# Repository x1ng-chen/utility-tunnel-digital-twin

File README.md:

# 综合管廊数字孪生与三Agent运维系统

面向综合管廊教学台架与智能运维演示，连接 **30路启用传感器、四块STM32、ESP32-S3网关、三维孪生、三Agent工作流和“小管”语音终端**。

[参赛版项目总览](docs/competition-final/01-项目总览.md) · [Agent 技术详解](docs/competition-final/05-Agent技术亮点与实现.md) · [当前进度](docs/PROJECT_STATUS.md) · [文档导航](docs/README.md) · [完整业务固件](firmware/four-controller/RELEASE.md) · [协作规范](CONTRIBUTING.md) · [版本记录](CHANGELOG.md)

> 参赛版 · 2026-11-07。11 月 6 日完成两轮 P5 实物告警、三维定位、真实三 Agent 排障与人工结单。第二轮核对 38 条平台观测与网关 MQTT 报文。模型复核仍要求补证，人工另行记录现场核对结果后完成工单。[实测记录](docs/competition-final/03-P5实物验收与证据.md)

*工作台截图来自2026-10-29隔离模拟环境，不是实时硬件状态。*

## 当前能力

| 模块 | 已具备的能力 | 验证与限制 |
| --- | --- | --- |
| 三Agent运维 | 取证→诊断→复核；工具轨迹、引用、快照与版本可追溯 | P5 两轮真实 DeepSeek 三角色均有输出，最终复核要求修改；独立人工评分待完成 |
| 可续查排障 | 候选原因、反证、缺项、人工检查反馈、新快照续查 | 人工报告不冒充仪表测量，不自动结单 |
| 受控经验与流程 | 候选提取、管理员审核、版本与来源匹配、退役 | 未审批内容不注入；复核通过不等于根因已证实 |
| 本地只读决策 | AnyJev/Tacit闭集检查选择、超时或不合格回退 | 默认关闭，不替代诊断模型，不具有任意控制权限 |
| 三维孪生 | V24统一编号、31路独立定位、明显告警高亮、风机状态呈现 | 五路火焰触发/定位/恢复获用户确认；其他逐路验收未齐 |
| 现场采集 | 四STM32分区采集，RS-485→单S3网关→MQTT→Django | 已有四板上报记录；CTRL-02 温湿度已停用，四板仍持续上报 |
| 双风机 | 固件支持继电器、反相PWM、TACH与INA226反馈 | 用户确认两台曾转动；调速、测速、支路电流精度仍待验收 |
| 小管语音 | 独立 S3 语音终端、唤醒、OLED、音量与站点只读巡检 | 现场已听到 P5 播报；语音端不负责设备控制与工单操作 |
| 仿真与成本 | 人工确认的仿真处置、回执复盘、双风机能耗/任务成本 | 模拟、假设与实测分别展示，不宣称真实节能收益 |

## 架构

```mermaid
flowchart LR
  S[五检测站 / 30路启用] --> C[4 × STM32F103RCT6]
  C <-->|RS-485 / Modbus RTU| G[ESP32-S3汇总网关]
  G -->|Wi-Fi / MQTT| M[MQTT接入服务]
  M --> D[Django / 数据与权限]
  D <--> W[Vue / Three.js / Agent工作台]
  D <--> A[取证Agent → 诊断Agent → 复核Agent]
  A --> E[证据护栏 / 知识检索 / 审核经验]
  V[另一块ESP32-S3语音终端] <--> VS[小管语音服务]
  VS <--> D
```

设备命令、命令回执、输出状态、独立转速反馈和告警恢复是不同证据。**实物只读联调不开放网页硬件控制；仿真执行不计作真实MQTT/RS-485验收。**

## 实体与身份基线

实体外形 **700 × 700 × 300 mm**，四角主控、五检测站，两台排风机，无水泵。传感器为液位4、温湿度4、MQ-2/MQ-4/MQ-7各5、火焰5、氧气3，共31个登记点位。2号板温湿度已停用，当前启用30路。两路INA226独立统计。

| 主控 | 电气布局位置 | 物理传感器数 | 主要设备 |
| --- | --- | ---: | --- |
| CTRL-01 | 左下 | 11 | 状态副屏 |
| CTRL-02 | 右下 | 7 | 主屏、摇杆、FAN-02、继电器2、INA226-FAN2 |
| CTRL-03 | 右上 | 6 | 蜂鸣器、灯带 |
| CTRL-04 | 左上 | 7 | FAN-01、继电器1、INA226-FAN1 |

采集编号、平台资产编码、模型文字及网格绑定通过版本化清单对应；不根据数组顺序重编号。P5没有温湿度模块。实物前端使用V24统一编号；隔离软件演示仍支持按精确SHA安装V24，不能混用映射。

[接线与引脚](docs/hardware/four-controller-wiring-20261026/README.md) · [风机/继电器/INA接线](docs/hardware/fan-relay-ina226-wiring-20261029.md) · [模型版本](model/README.md)

## 获取与启动

```powershell
git clone https://github.com/x1ng-chen/utility-tunnel-digital-twin.git
cd utility-tunnel-digital-twin
git lfs install
git lfs pull
```

需要Python 3.12、Node.js 22或更高兼容版本、Git LFS。嵌入式构建另需ARM GCC、CMake、Ninja与PlatformIO；依赖以各模块锁文件为准。

| 使用方式 | 入口 | 数据与权限 |
| --- | --- | --- |
| 隔离软件演示 | [Windows/Docker启动](deploy/agent-demo/README.md)；默认 `http://127.0.0.1:5187/agent-workbench` | 模拟库；模型调用默认关闭，需显式启用 |
| 参赛评审版 | [独立部署](deploy/competition-review/README.md) · [评审操作](docs/competition-final/04-比赛提交与评审演示.md) | P5 历史实测回放，查看者可运行只读 Agent 任务。公网地址需实测验收 |
| 实物只读联调 | [启动说明](deploy/hardware-live/README.md)；默认前端5173/API8000 | `.hardware-live/`独立库；不发布硬件命令 |
| 小管语音 | [语音服务](services/README.md) 与 [语音终端](firmware/README.md) | 使用独立S3，沿用其专门配置与启动说明 |
| 完整固件 | [构建/发布/刷写](firmware/four-controller/RELEASE.md) | 四STM32＋网关业务镜像；2号不使用最小诊断版作发布镜像 |

**账号、密码、Wi-Fi及MQTT凭据不放在主页或固件中。** 启动器生成的访问文件与`.env`仅保存在被忽略的本地运行目录。示例配置不包含真实密钥。

## 验证与待办

上一轮固件指纹和软件测试见[发布验证](docs/releases/2026-10-31/README.md)。本轮实物及模型记录见[P5 验收](docs/competition-final/03-P5实物验收与证据.md)。普通测试不调用付费模型、不连接真实执行器；浏览器、容器、真实模型与实物结论单独记录。

接下来优先完成：

1. 验收独立评审版公网登录、三维加载和巡检、排障、复核三项只读任务。
2. 双风机PWM/TACH和INA支路反馈专项验收，逐路完成其余传感器触发/恢复。
3. 显式启动真实DeepSeek回归、单/三Agent同数据对照及独立人工评分。
4. 整机断线恢复及连续运行复测。

K210视觉、趋势预测、MCP和寿命预测未纳入当前交付；仓库历史规划不代表这些功能已实现。

## 仓库结构

```text
backend/       Django API、三Agent、权限、场景与评测
frontend/      Vue工作台、Three.js孪生及界面测试
firmware/      四主控/网关业务源码、语音终端及历史固件
services/      MQTT接入、本地决策、语音服务
model/         V24统一编号及保留的历史模型交付
hardware/      硬件设计与说明
deploy/        隔离演示、只读联调和部署工具
docs/          当前进度、模块说明、验证记录与历史资料
tools/         质量门禁、模型检查与复现工具
```

旧README已归档到[历史说明](docs/history/README-before-20261031.md)。涉及双节点、旧模型、旧引脚和旧验收的记录保留出处，不作为当前操作依据。

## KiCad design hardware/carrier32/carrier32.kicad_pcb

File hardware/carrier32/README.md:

# Carrier32 KiCad 工程

本目录实现 `docs/superpowers/specs/2026-09-22-dual-node-32-sensor-carrier-design.md`。

## 工具链

- KiCad 10.0.5：`D:\KiCad\bin\kicad-cli.exe`
- Python 3：设计输入、网络合同及制造包检查脚本
- PowerShell：统一检查入口 `scripts/run_checks.ps1`

已安装的辅助能力包括 `kicad-tool`、`kicad-workflow`、
`kicad-sch-cleanup-loop`、`manage-pcba-program`、
`qualify-pcba-sourcing`、`design-and-review-circuit`、
`schematic-humanizer`、`pcb-layout-review`、
`release-pcba-fabrication`，以及 kicad-happy 的 `kicad`、`emc`、`bom`。
这些能力从下一轮 Codex 技能加载起可用。

## 运行检查

仅检查本机工具和工程骨架：

```powershell
powershell -ExecutionPolicy Bypass -File hardware/carrier32/scripts/run_checks.ps1 -Preflight
```

目前已经建立受保护的 12 V 输入、两路独立 5 V 降压和两路 ESP 3.3 V
电源原理图草稿，见 [电源审查记录](docs/power-review.md)。`scripts/check_power_nets.ps1`
对电源网表执行 80 项引脚映射断言；当前 ERC 为 0 错误、10 个尚未接到后续接口的警告。
导出的图面仍拥挤且标题栏未清理，因此尚未通过视觉审查。

32 个传感器数量和 MCU 引脚分配已锁定在 `config/net-contract.csv`，
不包含 DHT11。载板端 32 个统一四针传感器接口及线束边界见
[参考接口标准](docs/reference-interface-standard.md)和 `config/connector-contract.csv`；
运行 `python hardware/carrier32/scripts/check_connector_contract.py hardware/carrier32/config/connector-contract.csv hardware/carrier32/config/net-contract.csv`
可检查针位分配。完整工程检查在原理图、PCB和制造包补齐后启用。

## 当前发布状态

工程处于设计阶段。`config/design-inputs.csv` 中有 39 项制造关键实测输入尚未验证，
其中包括控制板排针、各类传感器模块引脚顺序、输出电压和机箱尺寸。
这些信息无法由软件或通用器件资料安全推断。机械尺寸、模块引脚、电气额定值及样板负载测试未完成前，
不得把本目录的任何输出作为可投产制造包。

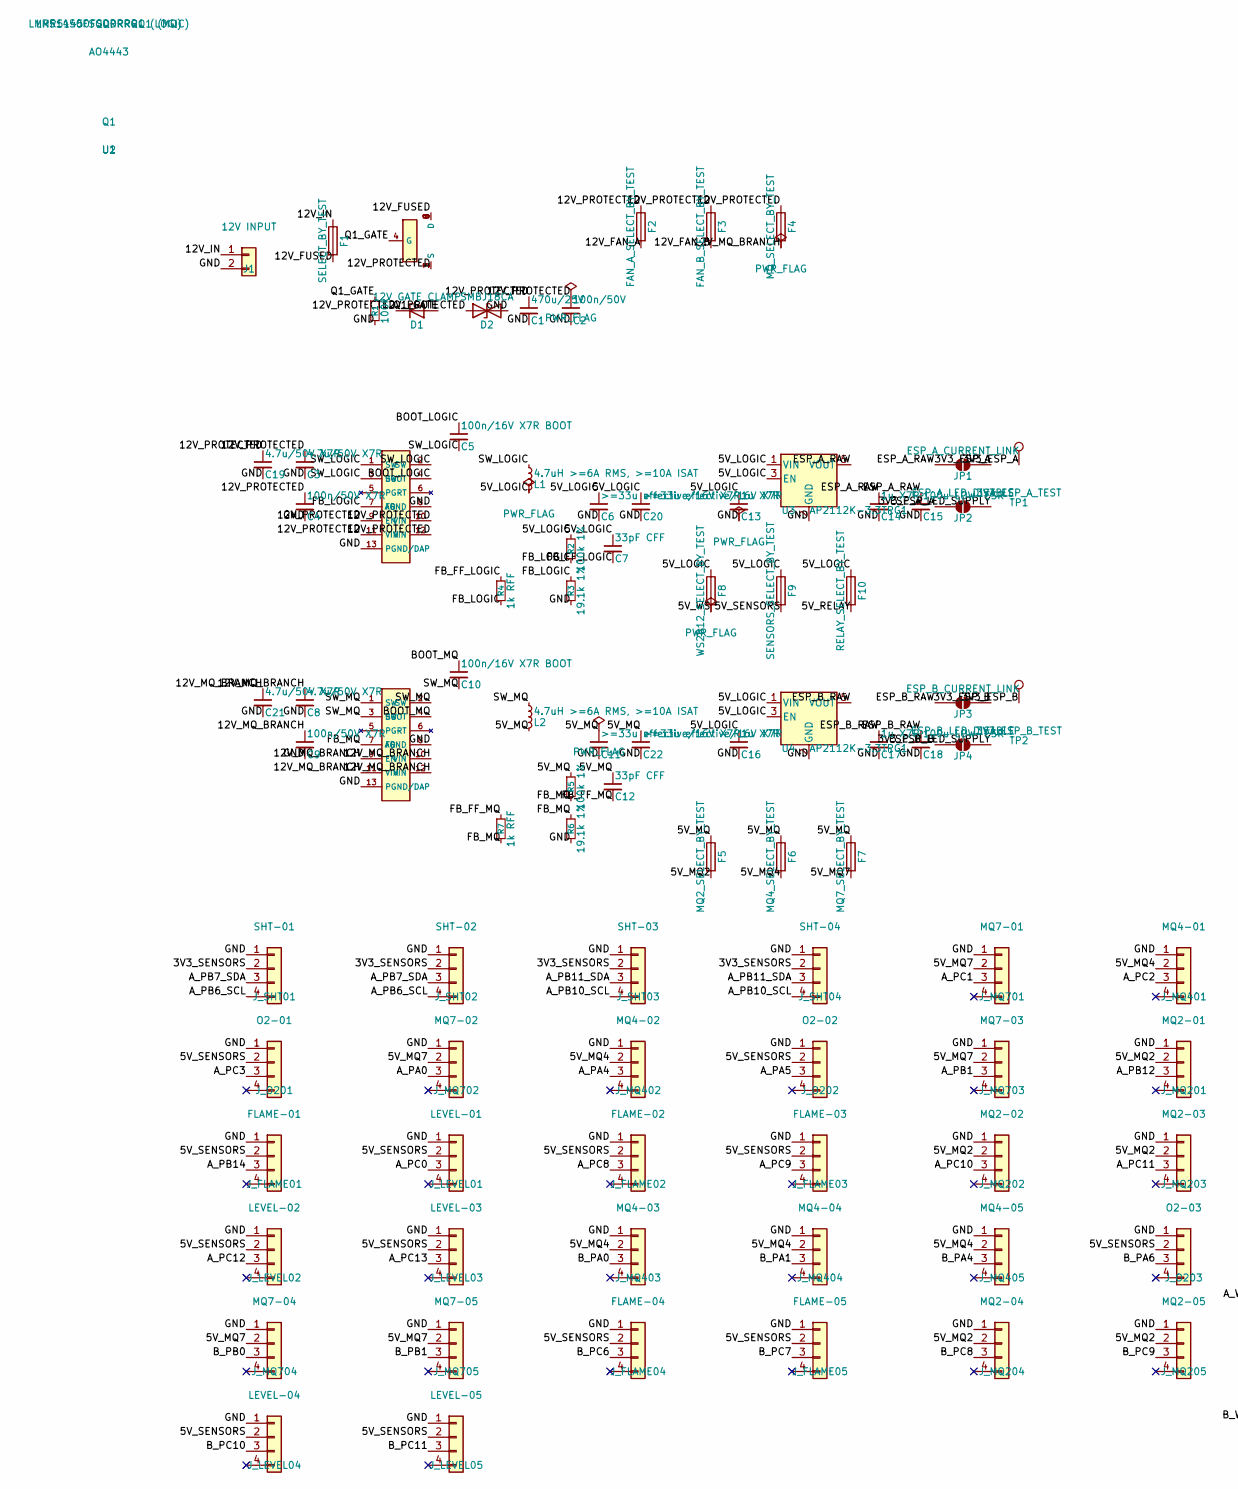
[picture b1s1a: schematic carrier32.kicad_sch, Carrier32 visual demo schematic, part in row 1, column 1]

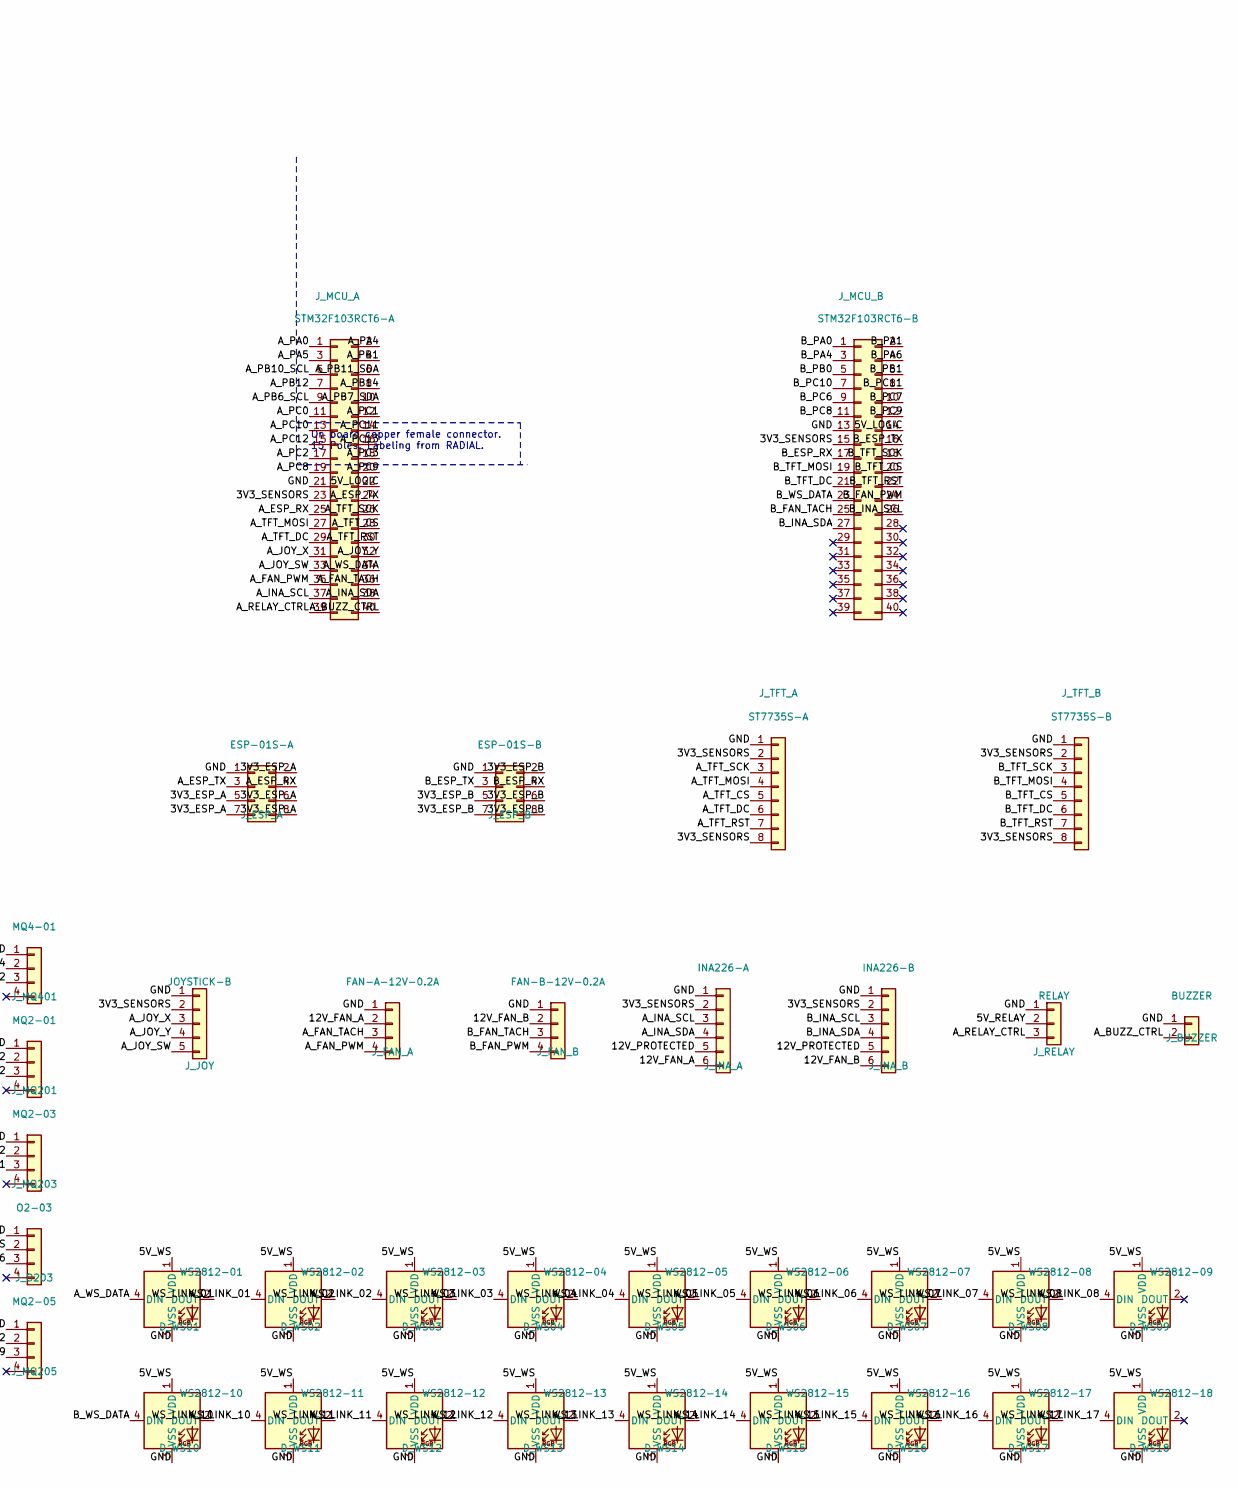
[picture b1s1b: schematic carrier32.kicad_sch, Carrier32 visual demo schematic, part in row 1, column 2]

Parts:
C1: 470u/25V; CP_Elec_10x10
C2: 100n/50V; C_0603_1608Metric
C3, C8, C19, C21: 4.7u/50V X7R; C_1210_3225Metric
C4, C9: 100n/50V X7R; C_0603_1608Metric
C5, C10: 100n/16V X7R BOOT; C_0603_1608Metric
C6, C11, C20, C22: >=33u effective/16V X7R; C_1210_3225Metric
C7, C12: 33pF CFF; C_0603_1608Metric
C13, C14, C16, C17: 1u X7R; C_0603_1608Metric
C15, C18: 100u LOW-ESR; CP_Elec_6.3x5.8
D1: 12V GATE CLAMP; D_SOD-123
D2: SMBJ18CA; D_SMB
D_WS01: WS2812-01; LED_WS2812B_PLCC4_5.0x5.0mm_P3.2mm
D_WS02: WS2812-02; LED_WS2812B_PLCC4_5.0x5.0mm_P3.2mm
D_WS03: WS2812-03; LED_WS2812B_PLCC4_5.0x5.0mm_P3.2mm
D_WS04: WS2812-04; LED_WS2812B_PLCC4_5.0x5.0mm_P3.2mm
D_WS05: WS2812-05; LED_WS2812B_PLCC4_5.0x5.0mm_P3.2mm
D_WS06: WS2812-06; LED_WS2812B_PLCC4_5.0x5.0mm_P3.2mm
D_WS07: WS2812-07; LED_WS2812B_PLCC4_5.0x5.0mm_P3.2mm
D_WS08: WS2812-08; LED_WS2812B_PLCC4_5.0x5.0mm_P3.2mm
D_WS09: WS2812-09; LED_WS2812B_PLCC4_5.0x5.0mm_P3.2mm
D_WS10: WS2812-10; LED_WS2812B_PLCC4_5.0x5.0mm_P3.2mm
D_WS11: WS2812-11; LED_WS2812B_PLCC4_5.0x5.0mm_P3.2mm
D_WS12: WS2812-12; LED_WS2812B_PLCC4_5.0x5.0mm_P3.2mm
D_WS13: WS2812-13; LED_WS2812B_PLCC4_5.0x5.0mm_P3.2mm
D_WS14: WS2812-14; LED_WS2812B_PLCC4_5.0x5.0mm_P3.2mm
D_WS15: WS2812-15; LED_WS2812B_PLCC4_5.0x5.0mm_P3.2mm
D_WS16: WS2812-16; LED_WS2812B_PLCC4_5.0x5.0mm_P3.2mm
D_WS17: WS2812-17; LED_WS2812B_PLCC4_5.0x5.0mm_P3.2mm
D_WS18: WS2812-18; LED_WS2812B_PLCC4_5.0x5.0mm_P3.2mm
F1: SELECT_BY_TEST; Fuse_1210_3225Metric
F2: FAN_A_SELECT_BY_TEST; Fuse_1210_3225Metric
F3: FAN_B_SELECT_BY_TEST; Fuse_1210_3225Metric
F4: MQ_SELECT_BY_TEST; Fuse_1210_3225Metric
F5: MQ2_SELECT_BY_TEST; Fuse_1210_3225Metric
F6: MQ4_SELECT_BY_TEST; Fuse_1210_3225Metric
F7: MQ7_SELECT_BY_TEST; Fuse_1210_3225Metric
F8: WS2812_SELECT_BY_TEST; Fuse_1210_3225Metric
F9: SENSORS_SELECT_BY_TEST; Fuse_1210_3225Metric
F10: RELAY_SELECT_BY_TEST; Fuse_1210_3225Metric
J1: 12V INPUT; TerminalBlock_Phoenix_MKDS-1,5-2_1x02_P5.00mm_Horizontal
JP1: ESP_A_CURRENT_LINK; SolderJumper-2_P1.3mm_Open_RoundedPad1.0x1.5mm
JP2: ESP_A_LED_DISABLE; SolderJumper-2_P1.3mm_Open_RoundedPad1.0x1.5mm
JP3: ESP_B_CURRENT_LINK; SolderJumper-2_P1.3mm_Open_RoundedPad1.0x1.5mm
JP4: ESP_B_LED_DISABLE; SolderJumper-2_P1.3mm_Open_RoundedPad1.0x1.5mm
J_BUZZER: BUZZER; PinSocket_1x02_P2.54mm_Vertical
J_ESP_A: ESP-01S-A; PinSocket_2x04_P2.54mm_Vertical
J_ESP_B: ESP-01S-B; PinSocket_2x04_P2.54mm_Vertical
J_FAN_A: FAN-A-12V-0.2A; JST_XH_B4B-XH-A_1x04_P2.50mm_Vertical
J_FAN_B: FAN-B-12V-0.2A; JST_XH_B4B-XH-A_1x04_P2.50mm_Vertical
J_FLAME01: FLAME-01; JST_XH_B4B-XH-A_1x04_P2.50mm_Vertical
J_FLAME02: FLAME-02; JST_XH_B4B-XH-A_1x04_P2.50mm_Vertical
J_FLAME03: FLAME-03; JST_XH_B4B-XH-A_1x04_P2.50mm_Vertical
J_FLAME04: FLAME-04; JST_XH_B4B-XH-A_1x04_P2.50mm_Vertical
J_FLAME05: FLAME-05; JST_XH_B4B-XH-A_1x04_P2.50mm_Vertical
J_INA_A: INA226-A; PinSocket_1x06_P2.54mm_Vertical
J_INA_B: INA226-B; PinSocket_1x06_P2.54mm_Vertical
J_JOY: JOYSTICK-B; PinSocket_1x05_P2.54mm_Vertical
J_LEVEL01: LEVEL-01; JST_XH_B4B-XH-A_1x04_P2.50mm_Vertical
J_LEVEL02: LEVEL-02; JST_XH_B4B-XH-A_1x04_P2.50mm_Vertical
J_LEVEL03: LEVEL-03; JST_XH_B4B-XH-A_1x04_P2.50mm_Vertical
J_LEVEL04: LEVEL-04; JST_XH_B4B-XH-A_1x04_P2.50mm_Vertical
J_LEVEL05: LEVEL-05; JST_XH_B4B-XH-A_1x04_P2.50mm_Vertical
J_MCU_A: STM32F103RCT6-A; PinSocket_2x20_P2.54mm_Vertical
J_MCU_B: STM32F103RCT6-B; PinSocket_2x20_P2.54mm_Vertical
J_MQ201: MQ2-01; JST_XH_B4B-XH-A_1x04_P2.50mm_Vertical
J_MQ202: MQ2-02; JST_XH_B4B-XH-A_1x04_P2.50mm_Vertical
J_MQ203: MQ2-03; JST_XH_B4B-XH-A_1x04_P2.50mm_Vertical
J_MQ204: MQ2-04; JST_XH_B4B-XH-A_1x04_P2.50mm_Vertical
J_MQ205: MQ2-05; JST_XH_B4B-XH-A_1x04_P2.50mm_Vertical
J_MQ401: MQ4-01; JST_XH_B4B-XH-A_1x04_P2.50mm_Vertical
J_MQ402: MQ4-02; JST_XH_B4B-XH-A_1x04_P2.50mm_Vertical
J_MQ403: MQ4-03; JST_XH_B4B-XH-A_1x04_P2.50mm_Vertical
J_MQ404: MQ4-04; JST_XH_B4B-XH-A_1x04_P2.50mm_Vertical
J_MQ405: MQ4-05; JST_XH_B4B-XH-A_1x04_P2.50mm_Vertical
J_MQ701: MQ7-01; JST_XH_B4B-XH-A_1x04_P2.50mm_Vertical
J_MQ702: MQ7-02; JST_XH_B4B-XH-A_1x04_P2.50mm_Vertical
J_MQ703: MQ7-03; JST_XH_B4B-XH-A_1x04_P2.50mm_Vertical
J_MQ704: MQ7-04; JST_XH_B4B-XH-A_1x04_P2.50mm_Vertical
J_MQ705: MQ7-05; JST_XH_B4B-XH-A_1x04_P2.50mm_Vertical
J_O201: O2-01; JST_XH_B4B-XH-A_1x04_P2.50mm_Vertical
J_O202: O2-02; JST_XH_B4B-XH-A_1x04_P2.50mm_Vertical
J_O203: O2-03; JST_XH_B4B-XH-A_1x04_P2.50mm_Vertical
J_RELAY: RELAY; PinSocket_1x03_P2.54mm_Vertical
J_SHT01: SHT-01; JST_XH_B4B-XH-A_1x04_P2.50mm_Vertical
J_SHT02: SHT-02; JST_XH_B4B-XH-A_1x04_P2.50mm_Vertical
J_SHT03: SHT-03; JST_XH_B4B-XH-A_1x04_P2.50mm_Vertical
J_SHT04: SHT-04; JST_XH_B4B-XH-A_1x04_P2.50mm_Vertical
J_TFT_A: ST7735S-A; PinSocket_1x08_P2.54mm_Vertical
J_TFT_B: ST7735S-B; PinSocket_1x08_P2.54mm_Vertical
L1, L2: 4.7uH >=6A RMS, >=10A ISAT; L_Abracon_ASPI-0628
Q1: AO4443; SOIC-8_3.9x4.9mm_P1.27mm
R1: 100k; R_0603_1608Metric
R2, R5: 100k 1%; R_0603_1608Metric
R3, R6: 19.1k 1%; R_0603_1608Metric
R4, R7: 1k RFF; R_0603_1608Metric
TP1: 3V3_ESP_A_TEST; TestPoint_Plated_Hole_D2.0mm
TP2: 3V3_ESP_B_TEST; TestPoint_Plated_Hole_D2.0mm
U1: LMR51450FSQDRRRQ1 (LOGIC); LMR51450_visual_13pin
U2: LMR51450FSQDRRRQ1 (MQ); LMR51450_visual_13pin
U3, U4: AP2112K-3.3TRG1; SOT-23-5

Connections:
/3V3_ESP_A: JP1.2 (B), JP2.1 (A), J_ESP_A.2, J_ESP_A.5, J_ESP_A.6, J_ESP_A.7, J_ESP_A.8, TP1.1 (1_1)
/3V3_ESP_B: JP3.2 (B), JP4.1 (A), J_ESP_B.2, J_ESP_B.5, J_ESP_B.6, J_ESP_B.7, J_ESP_B.8, TP2.1 (1_1)
/3V3_SENSORS: J_INA_A.2, J_INA_B.2, J_JOY.2, J_MCU_A.23, J_MCU_B.15, J_SHT01.2, J_SHT02.2, J_SHT03.2, J_SHT04.2, J_TFT_A.2, J_TFT_A.8, J_TFT_B.2, J_TFT_B.8
/5V_LOGIC: C6.1, C7.1, C13.1, C16.1, C20.1, F8.1, F9.1, F10.1, J_MCU_A.22, J_MCU_B.14, L1.2, R2.1, U3.1 (VIN), U3.3 (EN), U4.1 (VIN), U4.3 (EN)
/5V_MQ: C11.1, C12.1, C22.1, F5.1, F6.1, F7.1, L2.2, R5.1
/5V_MQ2: F5.2, J_MQ201.2, J_MQ202.2, J_MQ203.2, J_MQ204.2, J_MQ205.2
/5V_MQ4: F6.2, J_MQ401.2, J_MQ402.2, J_MQ403.2, J_MQ404.2, J_MQ405.2
/5V_MQ7: F7.2, J_MQ701.2, J_MQ702.2, J_MQ703.2, J_MQ704.2, J_MQ705.2
/5V_RELAY: F10.2, J_RELAY.2
/5V_SENSORS: F9.2, J_FLAME01.2, J_FLAME02.2, J_FLAME03.2, J_FLAME04.2, J_FLAME05.2, J_LEVEL01.2, J_LEVEL02.2, J_LEVEL03.2, J_LEVEL04.2, J_LEVEL05.2, J_O201.2, J_O202.2, J_O203.2
/5V_WS: D_WS01.1 (VDD), D_WS02.1 (VDD), D_WS03.1 (VDD), D_WS04.1 (VDD), D_WS05.1 (VDD), D_WS06.1 (VDD), D_WS07.1 (VDD), D_WS08.1 (VDD), D_WS09.1 (VDD), D_WS10.1 (VDD), D_WS11.1 (VDD), D_WS12.1 (VDD), D_WS13.1 (VDD), D_WS14.1 (VDD), D_WS15.1 (VDD), D_WS16.1 (VDD), D_WS17.1 (VDD), D_WS18.1 (VDD), F8.2
/12V_FAN_A: F2.2, J_FAN_A.2, J_INA_A.6
/12V_FAN_B: F3.2, J_FAN_B.2, J_INA_B.6
/12V_FUSED: F1.2, Q1.5 (D), Q1.6 (D), Q1.7 (D), Q1.8 (D)
/12V_IN: F1.1, J1.1
/12V_MQ_BRANCH: C8.1, C9.1, C21.1, F4.2, U2.9 (EN), U2.10 (VIN), U2.11 (VIN), U2.12 (VIN)
/12V_PROTECTED: C1.1, C2.1, C3.1, C4.1, C19.1, D1.1 (K), D2.1 (A1), F2.1, F3.1, F4.1, J_INA_A.5, J_INA_B.5, Q1.1 (S), Q1.2 (S), Q1.3 (S), U1.9 (EN), U1.10 (VIN), U1.11 (VIN), U1.12 (VIN)
/A_BUZZ_CTRL: J_BUZZER.2, J_MCU_A.40
/A_ESP_RX: J_ESP_A.4, J_MCU_A.25
/A_ESP_TX: J_ESP_A.3, J_MCU_A.24
/A_FAN_PWM: J_FAN_A.4, J_MCU_A.35
/A_FAN_TACH: J_FAN_A.3, J_MCU_A.36
/A_INA_SCL: J_INA_A.3, J_MCU_A.37
/A_INA_SDA: J_INA_A.4, J_MCU_A.38
/A_JOY_SW: J_JOY.5, J_MCU_A.33
/A_JOY_X: J_JOY.3, J_MCU_A.31
/A_JOY_Y: J_JOY.4, J_MCU_A.32
/A_PA0: J_MCU_A.1, J_MQ702.3
/A_PA4: J_MCU_A.2, J_MQ402.3
/A_PA5: J_MCU_A.3, J_O202.3
/A_PB1: J_MCU_A.4, J_MQ703.3
/A_PB6_SCL: J_MCU_A.9, J_SHT01.4, J_SHT02.4
/A_PB7_SDA: J_MCU_A.10, J_SHT01.3, J_SHT02.3
/A_PB10_SCL: J_MCU_A.5, J_SHT03.4, J_SHT04.4
/A_PB11_SDA: J_MCU_A.6, J_SHT03.3, J_SHT04.3
/A_PB12: J_MCU_A.7, J_MQ201.3
/A_PB14: J_FLAME01.3, J_MCU_A.8
/A_PC0: J_LEVEL01.3, J_MCU_A.11
/A_PC1: J_MCU_A.12, J_MQ701.3
/A_PC2: J_MCU_A.17, J_MQ401.3
/A_PC3: J_MCU_A.18, J_O201.3
/A_PC8: J_FLAME02.3, J_MCU_A.19
/A_PC9: J_FLAME03.3, J_MCU_A.20
/A_PC10: J_MCU_A.13, J_MQ202.3
/A_PC11: J_MCU_A.14, J_MQ203.3
/A_PC12: J_LEVEL02.3, J_MCU_A.15
/A_PC13: J_LEVEL03.3, J_MCU_A.16
/A_RELAY_CTRL: J_MCU_A.39, J_RELAY.3
/A_TFT_CS: J_MCU_A.28, J_TFT_A.5
/A_TFT_DC: J_MCU_A.29, J_TFT_A.6
/A_TFT_MOSI: J_MCU_A.27, J_TFT_A.4
/A_TFT_RST: J_MCU_A.30, J_TFT_A.7
/A_TFT_SCK: J_MCU_A.26, J_TFT_A.3
/A_WS_DATA: D_WS01.4 (DIN), J_MCU_A.34
/BOOT_LOGIC: C5.1, U1.4 (BOOT)
/BOOT_MQ: C10.1, U2.4 (BOOT)
/B_ESP_RX: J_ESP_B.4, J_MCU_B.17
/B_ESP_TX: J_ESP_B.3, J_MCU_B.16
/B_FAN_PWM: J_FAN_B.4, J_MCU_B.24
/B_FAN_TACH: J_FAN_B.3, J_MCU_B.25
/B_INA_SCL: J_INA_B.3, J_MCU_B.26
/B_INA_SDA: J_INA_B.4, J_MCU_B.27
/B_PA0: J_MCU_B.1, J_MQ403.3
/B_PA1: J_MCU_B.2, J_MQ404.3
/B_PA4: J_MCU_B.3, J_MQ405.3
/B_PA6: J_MCU_B.4, J_O203.3
/B_PB0: J_MCU_B.5, J_MQ704.3
/B_PB1: J_MCU_B.6, J_MQ705.3
/B_PC6: J_FLAME04.3, J_MCU_B.9
/B_PC7: J_FLAME05.3, J_MCU_B.10
/B_PC8: J_MCU_B.11, J_MQ204.3
/B_PC9: J_MCU_B.12, J_MQ205.3
/B_PC10: J_LEVEL04.3, J_MCU_B.7
/B_PC11: J_LEVEL05.3, J_MCU_B.8
/B_TFT_CS: J_MCU_B.20, J_TFT_B.5
/B_TFT_DC: J_MCU_B.21, J_TFT_B.6
/B_TFT_MOSI: J_MCU_B.19, J_TFT_B.4
/B_TFT_RST: J_MCU_B.22, J_TFT_B.7
/B_TFT_SCK: J_MCU_B.18, J_TFT_B.3
/B_WS_DATA: D_WS10.4 (DIN), J_MCU_B.23
/ESP_A_LED_SUPPLY: JP2.2 (B)
/ESP_A_RAW: C14.1, C15.1, JP1.1 (A), U3.5 (VOUT)
/ESP_B_LED_SUPPLY: JP4.2 (B)
/ESP_B_RAW: C17.1, C18.1, JP3.1 (A), U4.5 (VOUT)
/FB_FF_LOGIC: C7.2, R4.1
/FB_FF_MQ: C12.2, R7.1
/FB_LOGIC: R2.2, R3.1, R4.2, U1.7 (FB)
/FB_MQ: R5.2, R6.1, R7.2, U2.7 (FB)
/GND: C1.2, C2.2, C3.2, C4.2, C6.2, C8.2, C9.2, C11.2, C13.2, C14.2, C15.2, C16.2, C17.2, C18.2, C19.2, C20.2, C21.2, C22.2, D2.2 (A2), D_WS01.3 (VSS), D_WS02.3 (VSS), D_WS03.3 (VSS), D_WS04.3 (VSS), D_WS05.3 (VSS), D_WS06.3 (VSS), D_WS07.3 (VSS), D_WS08.3 (VSS), D_WS09.3 (VSS), D_WS10.3 (VSS), D_WS11.3 (VSS), D_WS12.3 (VSS), D_WS13.3 (VSS), D_WS14.3 (VSS), D_WS15.3 (VSS), D_WS16.3 (VSS), D_WS17.3 (VSS), D_WS18.3 (VSS), J1.2, J_BUZZER.1, J_ESP_A.1, J_ESP_B.1, J_FAN_A.1, J_FAN_B.1, J_FLAME01.1, J_FLAME02.1, J_FLAME03.1, J_FLAME04.1, J_FLAME05.1, J_INA_A.1, J_INA_B.1, J_JOY.1, J_LEVEL01.1, J_LEVEL02.1, J_LEVEL03.1, J_LEVEL04.1, J_LEVEL05.1, J_MCU_A.21, J_MCU_B.13, J_MQ201.1, J_MQ202.1, J_MQ203.1, J_MQ204.1, J_MQ205.1, J_MQ401.1, J_MQ402.1, J_MQ403.1, J_MQ404.1, J_MQ405.1, J_MQ701.1, J_MQ702.1, J_MQ703.1, J_MQ704.1, J_MQ705.1, J_O201.1, J_O202.1, J_O203.1, J_RELAY.1, J_SHT01.1, J_SHT02.1, J_SHT03.1, J_SHT04.1, J_TFT_A.1, J_TFT_B.1, R1.2, R3.2, R6.2, U1.8 (AGND), U1.13 (PGND/DAP), U2.8 (AGND), U2.13 (PGND/DAP), U3.2 (GND), U4.2 (GND)
/Q1_GATE: D1.2 (A), Q1.4 (G), R1.1
/SW_LOGIC: C5.2, L1.1, U1.1 (SW), U1.2 (SW), U1.3 (SW)
/SW_MQ: C10.2, L2.1, U2.1 (SW), U2.2 (SW), U2.3 (SW)
/WS_LINK_01: D_WS01.2 (DOUT), D_WS02.4 (DIN)
/WS_LINK_02: D_WS02.2 (DOUT), D_WS03.4 (DIN)
/WS_LINK_03: D_WS03.2 (DOUT), D_WS04.4 (DIN)
/WS_LINK_04: D_WS04.2 (DOUT), D_WS05.4 (DIN)
/WS_LINK_05: D_WS05.2 (DOUT), D_WS06.4 (DIN)
/WS_LINK_06: D_WS06.2 (DOUT), D_WS07.4 (DIN)
/WS_LINK_07: D_WS07.2 (DOUT), D_WS08.4 (DIN)
/WS_LINK_08: D_WS08.2 (DOUT), D_WS09.4 (DIN)
/WS_LINK_10: D_WS10.2 (DOUT), D_WS11.4 (DIN)
/WS_LINK_11: D_WS11.2 (DOUT), D_WS12.4 (DIN)
/WS_LINK_12: D_WS12.2 (DOUT), D_WS13.4 (DIN)
/WS_LINK_13: D_WS13.2 (DOUT), D_WS14.4 (DIN)
/WS_LINK_14: D_WS14.2 (DOUT), D_WS15.4 (DIN)
/WS_LINK_15: D_WS15.2 (DOUT), D_WS16.4 (DIN)
/WS_LINK_16: D_WS16.2 (DOUT), D_WS17.4 (DIN)
/WS_LINK_17: D_WS17.2 (DOUT), D_WS18.4 (DIN)

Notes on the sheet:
On board copper female connector. 15 Poles. Labeling from RADIAL.

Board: 4 copper layers, 118 parts (0 on the bottom side), 106 nets, no tracks yet.
